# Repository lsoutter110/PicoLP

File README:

# PicoLP

STM32 development board, designed within the Raspberry Pi Pico footprint.

## Getting Started

A pinout for the board is provided in `documentation`, and example projects are provided in `firmware`. To build an example using CMake/VSCode:
- Clone the repo
- Import the project with the STM32Cube extension
- Configure the build options when prompted (Debug/Release)
- Configure as default and run the Build+Flash task with the STLink attached to the board

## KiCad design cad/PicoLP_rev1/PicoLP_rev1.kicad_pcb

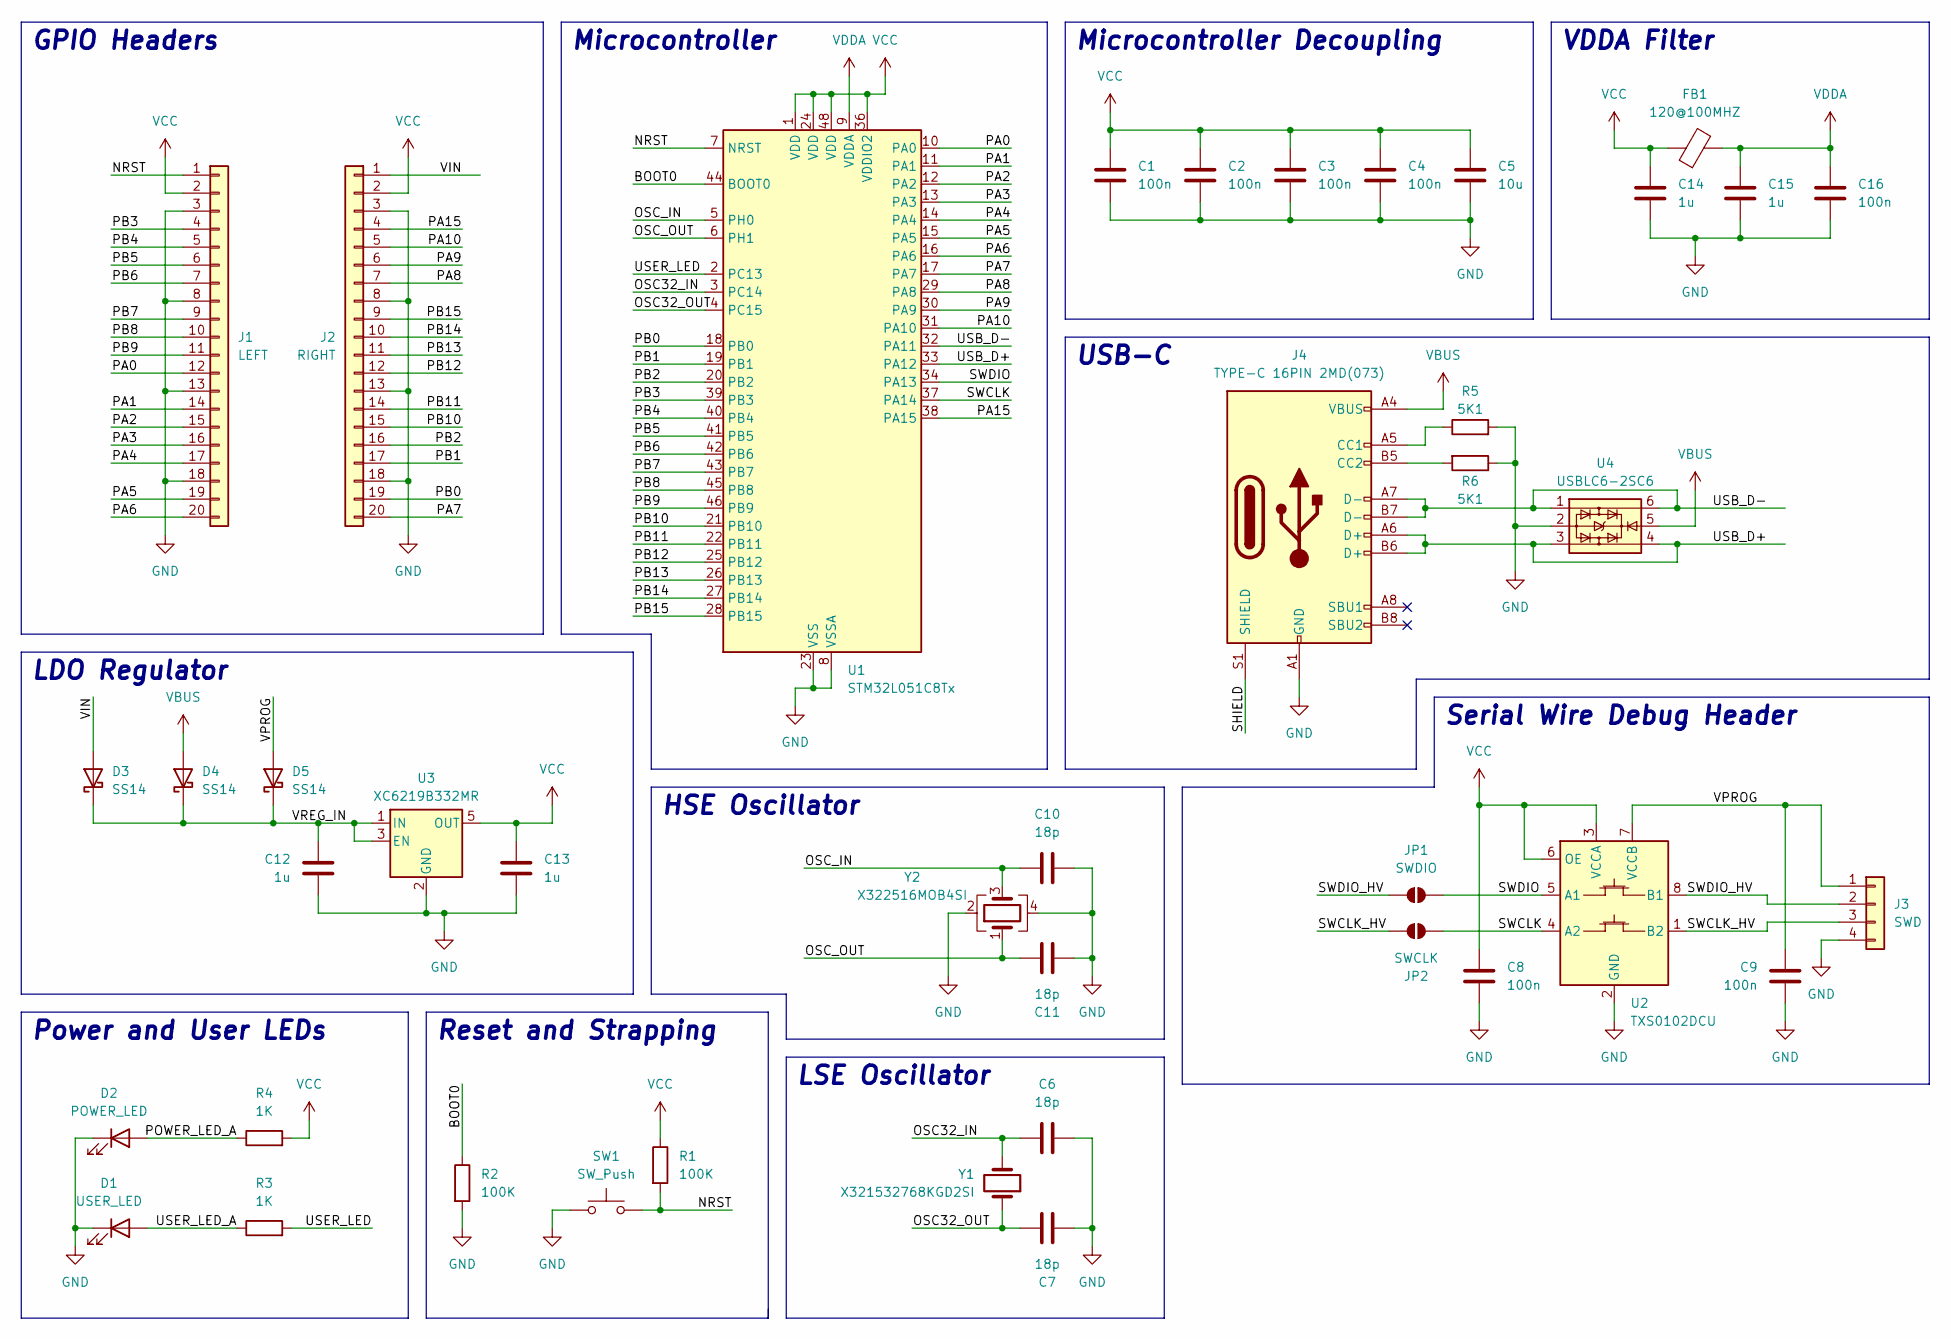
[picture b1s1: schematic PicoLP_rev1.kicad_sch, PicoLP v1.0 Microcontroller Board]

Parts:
C1, C2, C3, C4, C8, C9, C16: 100n; C_0402_1005Metric
C5: 10u; C_1206_3216Metric
C6, C7, C10, C11: 18p; C_0402_1005Metric
C12, C13, C14, C15: 1u; C_0603_1608Metric
D1: USER_LED; LED_0603_1608Metric
D2: POWER_LED; LED_0603_1608Metric
D3, D4, D5: SS14; D_SMA
FB1: 120@100MHZ; L_0603_1608Metric
J1: LEFT; PinHeader_1x20_P2.54mm_Vertical
J2: RIGHT; PinHeader_1x20_P2.54mm_Vertical
J3: SWD; PinHeader_1x04_P2.54mm_Vertical
J4: TYPE-C 16PIN 2MD(073); USB_C_Receptacle_GCT_USB4105-xx-A_16P_TopMnt_Horizontal
JP1: SWDIO; SolderJumper-2_P1.3mm_Open_TrianglePad1.0x1.5mm
JP2: SWCLK; SolderJumper-2_P1.3mm_Open_TrianglePad1.0x1.5mm
R1, R2: 100K; R_0603_1608Metric
R3, R4: 1K; R_0603_1608Metric
R5, R6: 5K1; R_0603_1608Metric
SW1: SW_Push; TS-1088
U1: STM32L051C8Tx; LQFP-48_7x7mm_P0.5mm
U2: TXS0102DCU; VSSOP-8_2.3x2mm_P0.5mm
U3: XC6219B332MR; SOT-23-5
U4: USBLC6-2SC6; SOT-23-6
Y1: X321532768KGD2SI; Crystal_SMD_3215-2Pin_3.2x1.5mm
Y2: X322516MOB4SI; Crystal_SMD_3225-4Pin_3.2x2.5mm

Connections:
/BOOT0: R2.1, U1.44 (BOOT0)
/NRST: J1.1, R1.2, SW1.2, U1.7 (NRST)
/OSC32_IN: C6.1, U1.3 (PC14), Y1.2
/OSC32_OUT: C7.1, U1.4 (PC15), Y1.1
/OSC_IN: C10.1, U1.5 (PH0), Y2.3
/OSC_OUT: C11.1, U1.6 (PH1), Y2.1
/PA0: J1.12, U1.10 (PA0)
/PA1: J1.14, U1.11 (PA1)
/PA2: J1.15, U1.12 (PA2)
/PA3: J1.16, U1.13 (PA3)
/PA4: J1.17, U1.14 (PA4)
/PA5: J1.19, U1.15 (PA5)
/PA6: J1.20, U1.16 (PA6)
/PA7: J2.20, U1.17 (PA7)
/PA8: J2.7, U1.29 (PA8)
/PA9: J2.6, U1.30 (PA9)
/PA10: J2.5, U1.31 (PA10)
/PA15: J2.4, U1.38 (PA15)
/PB0: J2.19, U1.18 (PB0)
/PB1: J2.17, U1.19 (PB1)
/PB2: J2.16, U1.20 (PB2)
/PB3: J1.4, U1.39 (PB3)
/PB4: J1.5, U1.40 (PB4)
/PB5: J1.6, U1.41 (PB5)
/PB6: J1.7, U1.42 (PB6)
/PB7: J1.9, U1.43 (PB7)
/PB8: J1.10, U1.45 (PB8)
/PB9: J1.11, U1.46 (PB9)
/PB10: J2.15, U1.21 (PB10)
/PB11: J2.14, U1.22 (PB11)
/PB12: J2.12, U1.25 (PB12)
/PB13: J2.11, U1.26 (PB13)
/PB14: J2.10, U1.27 (PB14)
/PB15: J2.9, U1.28 (PB15)
/POWER_LED_A: D2.2 (A), R4.1
/SHIELD: J4.S1 (SHIELD)
/SWCLK: JP2.2 (B), U1.37 (PA14), U2.4 (A2)
/SWCLK_HV: J3.3, JP2.1 (A), U2.1 (B2)
/SWDIO: JP1.2 (B), U1.34 (PA13), U2.5 (A1)
/SWDIO_HV: J3.2, JP1.1 (A), U2.8 (B1)
/USB_D+: J4.A6 (D+), J4.B6 (D+), U1.33 (PA12), U4.3, U4.4
/USB_D-: J4.A7 (D-), J4.B7 (D-), U1.32 (PA11), U4.1, U4.6
/USER_LED: R3.2, U1.2 (PC13)
/USER_LED_A: D1.2 (A), R3.1
/VIN: D3.2 (A), J2.1
/VPROG: C9.1, D5.2 (A), J3.1, U2.7 (VCCB)
/VREG_IN: C12.1, D3.1 (K), D4.1 (K), D5.1 (K), U3.1 (IN), U3.3 (EN)
GND: C1.2, C2.2, C3.2, C4.2, C5.2, C6.2, C7.2, C8.2, C9.2, C10.2, C11.2, C12.2, C13.2, C14.2, C15.2, C16.2, D1.1 (K), D2.1 (K), J1.3, J1.8, J1.13, J1.18, J2.3, J2.8, J2.13, J2.18, J3.4, J4.A1 (GND), J4.A12 (GND), J4.B1 (GND), J4.B12 (GND), R2.2, R5.2, R6.1, SW1.1, U1.8 (VSSA), U1.23 (VSS), U1.35 (VSS), U1.47 (VSS), U2.2 (GND), U3.2 (GND), U4.2, Y2.2, Y2.4
unnamed: J4.A5 (CC1), R5.1
unnamed: J4.B5 (CC2), R6.2
VBUS: D4.2 (A), J4.A4 (VBUS), J4.A9 (VBUS), J4.B4 (VBUS), J4.B9 (VBUS), U4.5
VCC: C1.1, C2.1, C3.1, C4.1, C5.1, C8.1, C13.1, C14.1, FB1.1, J1.2, J2.2, R1.1, R4.2, U1.1 (VDD), U1.24 (VDD), U1.36 (VDDIO2), U1.48 (VDD), U2.3 (VCCA), U2.6 (OE), U3.5 (OUT)
VDDA: C15.1, C16.1, FB1.2, U1.9 (VDDA)

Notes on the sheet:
Reset and Strapping
HSE Oscillator
Serial Wire Debug Header
GPIO Headers
LDO Regulator
LSE Oscillator
USB-C
Power and User LEDs
Microcontroller
VDDA Filter
Microcontroller Decoupling

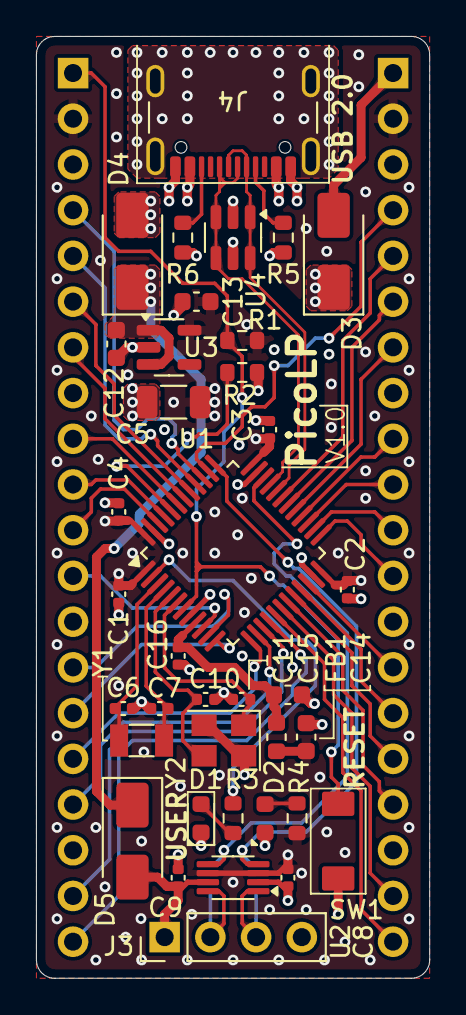
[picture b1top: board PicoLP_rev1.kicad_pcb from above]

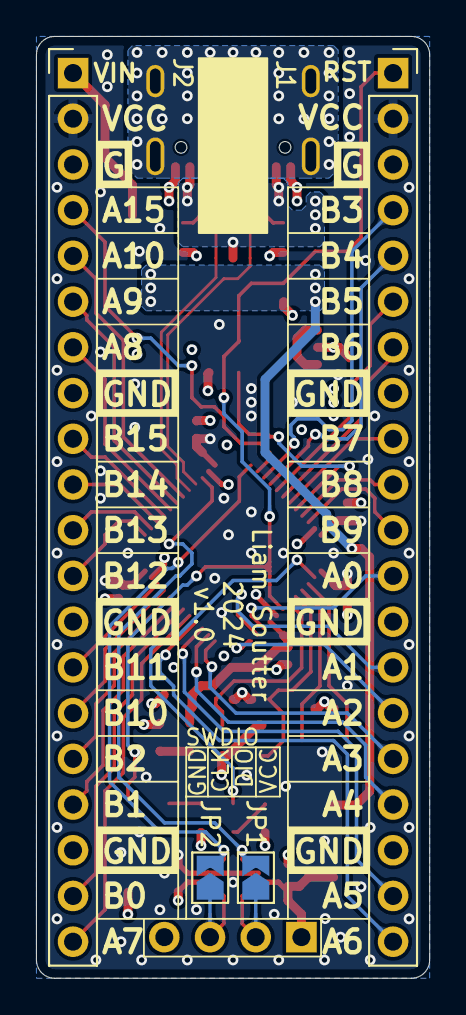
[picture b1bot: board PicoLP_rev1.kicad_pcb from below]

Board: 4 copper layers, 21.8 x 52.3 mm, 41 parts (4 on the bottom side), 52 nets.

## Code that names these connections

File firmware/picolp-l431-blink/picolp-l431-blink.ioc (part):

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Mcu.Name=STM32L431C(B-C)Tx
Mcu.Package=LQFP48
Mcu.UserName=STM32L431CCTx
PA10.Mode=Asynchronous
PA10.Signal=USART1_RX
PA13\ (JTMS-SWDIO).Mode=Serial_Wire
PA13\ (JTMS-SWDIO).Signal=SYS_JTMS-SWDIO
PA14\ (JTCK-SWCLK).Mode=Serial_Wire
PA14\ (JTCK-SWCLK).Signal=SYS_JTCK-SWCLK
PA9.Mode=Asynchronous
PA9.Signal=USART1_TX
PC13.GPIOParameters=GPIO_Label
PC13.GPIO_Label=USER_LED
PC13.Signal=GPIO_Output
PH0-OSC_IN\ (PH0).Mode=HSE-External-Oscillator
PH0-OSC_IN\ (PH0).Signal=RCC_OSC_IN
PH1-OSC_OUT\ (PH1).Mode=HSE-External-Oscillator
PH1-OSC_OUT\ (PH1).Signal=RCC_OSC_OUT
RCC.HSE_VALUE=16000000
RCC.SYSCLKFreq_VALUE=80000000
RCC.SYSCLKSource=RCC_SYSCLKSOURCE_PLLCLK
board=custom

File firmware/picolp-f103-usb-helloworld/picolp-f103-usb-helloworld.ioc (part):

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Mcu.Name=STM32F103C(8-B)Tx
Mcu.Package=LQFP48
Mcu.UserName=STM32F103CBTx
PA11.Mode=Device
PA11.Signal=USB_DM
PA12.Mode=Device
PA12.Signal=USB_DP
PA13.Mode=Serial_Wire
PA13.Signal=SYS_JTMS-SWDIO
PA14.Mode=Serial_Wire
PA14.Signal=SYS_JTCK-SWCLK
PC13-TAMPER-RTC.GPIOParameters=GPIO_Label
PC13-TAMPER-RTC.GPIO_Label=USER_LED
PC13-TAMPER-RTC.Signal=GPIO_Output
PD0-OSC_IN.Mode=HSE-External-Oscillator
PD0-OSC_IN.Signal=RCC_OSC_IN
PD1-OSC_OUT.Mode=HSE-External-Oscillator
PD1-OSC_OUT.Signal=RCC_OSC_OUT
RCC.HSEDivPLL=RCC_HSE_PREDIV_DIV2
RCC.HSE_VALUE=16000000
RCC.SYSCLKFreq_VALUE=72000000
RCC.SYSCLKSource=RCC_SYSCLKSOURCE_PLLCLK
board=custom

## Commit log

2025-10-26 PicoLP rev1 files and examples added
2025-10-26 Added a readme
2025-10-26 Changed readme file format to markdown
